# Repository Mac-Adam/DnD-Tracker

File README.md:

# DnD-Tracker
Repository for my resource tracker for D&amp;D
The premise of this project is to make keeping track of health, spell slots, and other resources quick and simple,
while preserving the vibe of an ttrpg.
It consists of 3 modules. One, keeps track of your health (3 led strips each one representing one digit of a 3 digit number)
Second one keeps track of your spell slots
The last one keeps track of whatever 20 resources you have, potions class features, magic items etc.
The rgb leds are driven by a 555 timer based circuit, this allows for controlling the color and brightness of the lights.
A standard 18650 cell is enough to power it for tens of hours (depending on the brightness level)
This project is not yet fully finished, the pcb and the files contain some errors that I haven't fixed yet.
The errors are:
  - Didn't reverse the logic of the LED ON button, insead of turning the leds off, it blasts them at full power
  - Transistors in one of the signal reperaters in the HP modules are switched (P is in flsae of N and N is in place of P)
  - The housing has misaligned mounting holes
## The Future
I might make the design modular, this would enable greater flexibility and probably would be cheaper.
Making the housing more practical and prettier.

If you want to build one of those yoursellf, but you encounter some problems with the provided files, contact me.

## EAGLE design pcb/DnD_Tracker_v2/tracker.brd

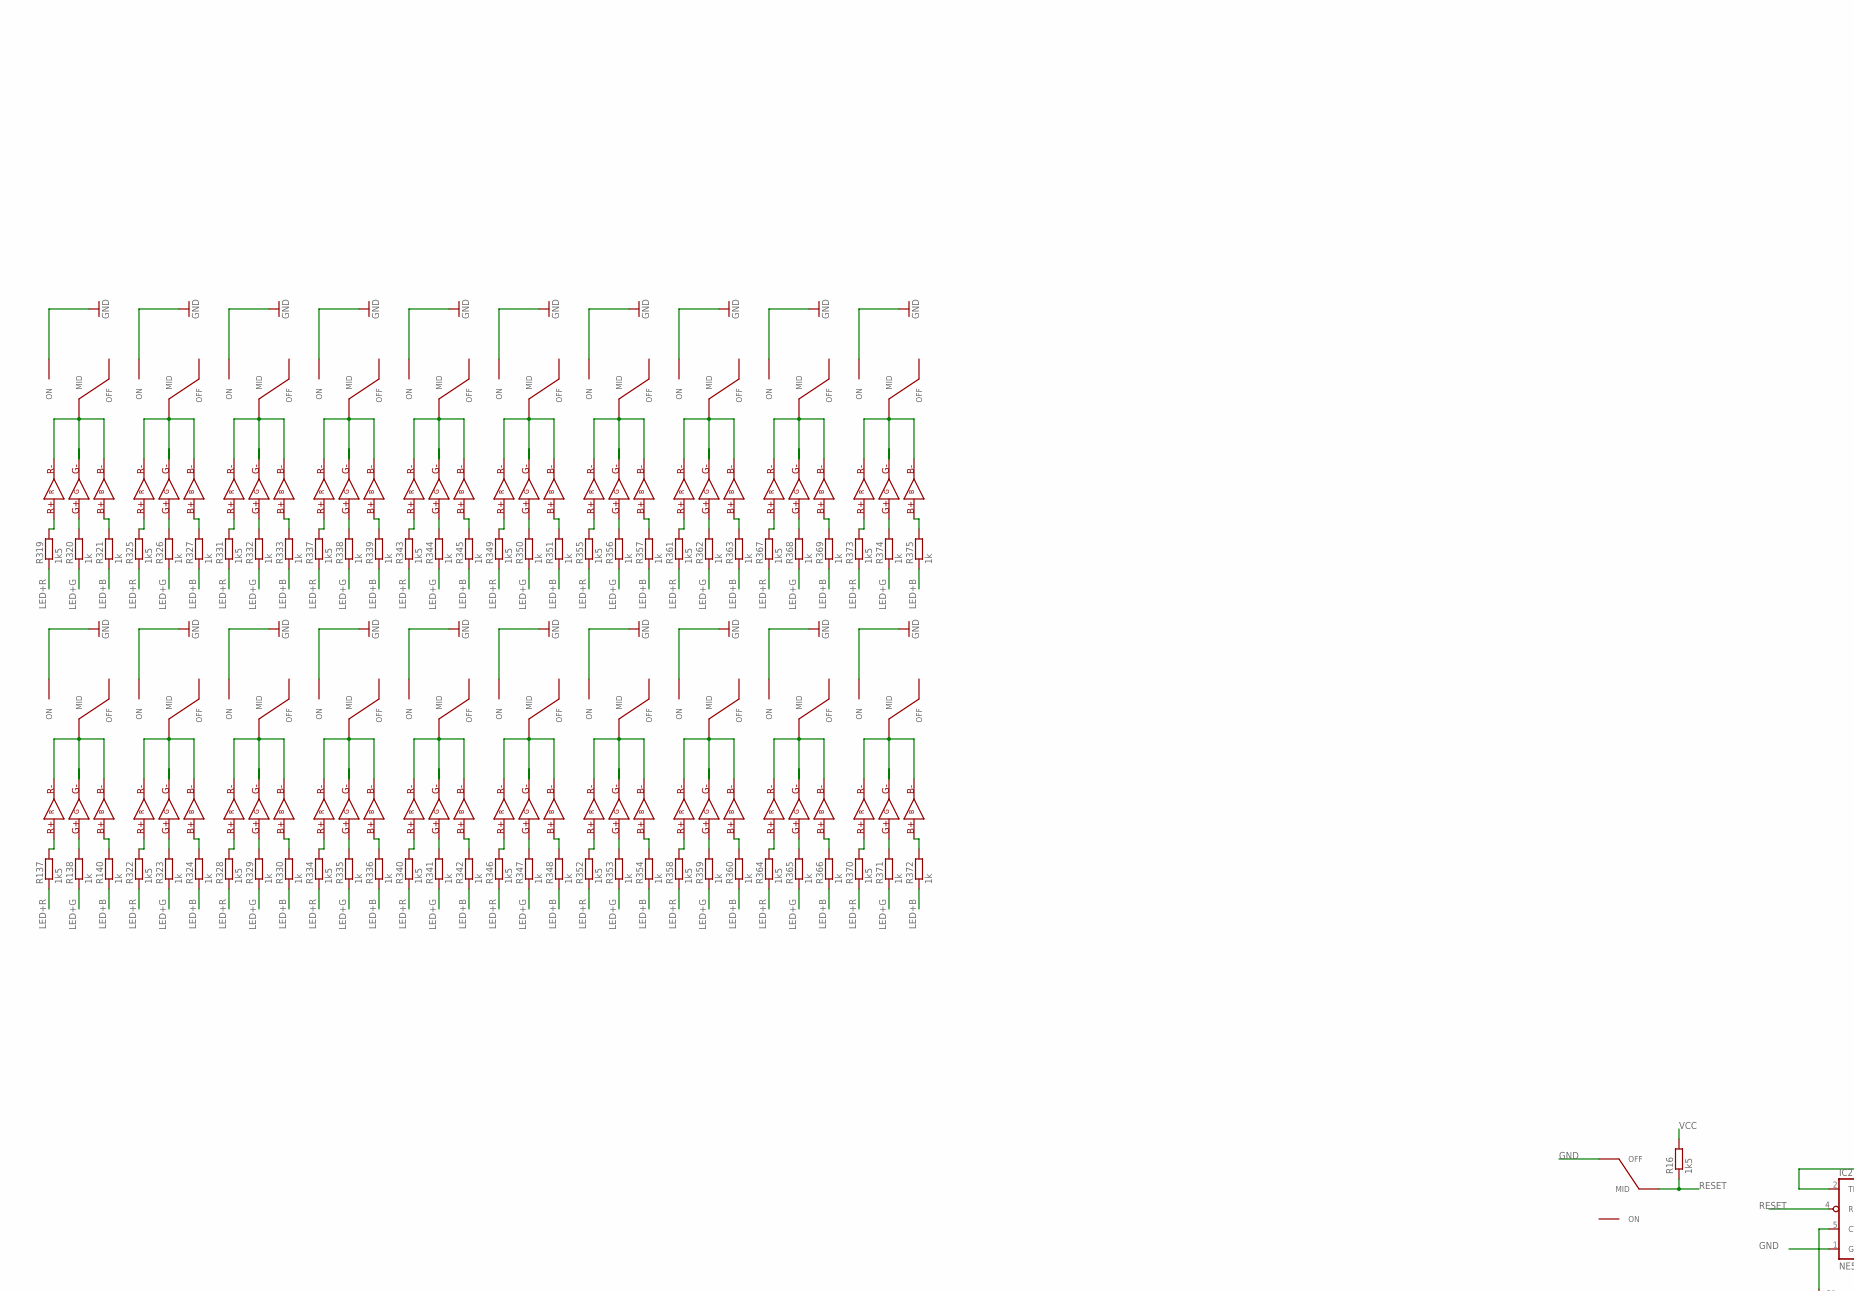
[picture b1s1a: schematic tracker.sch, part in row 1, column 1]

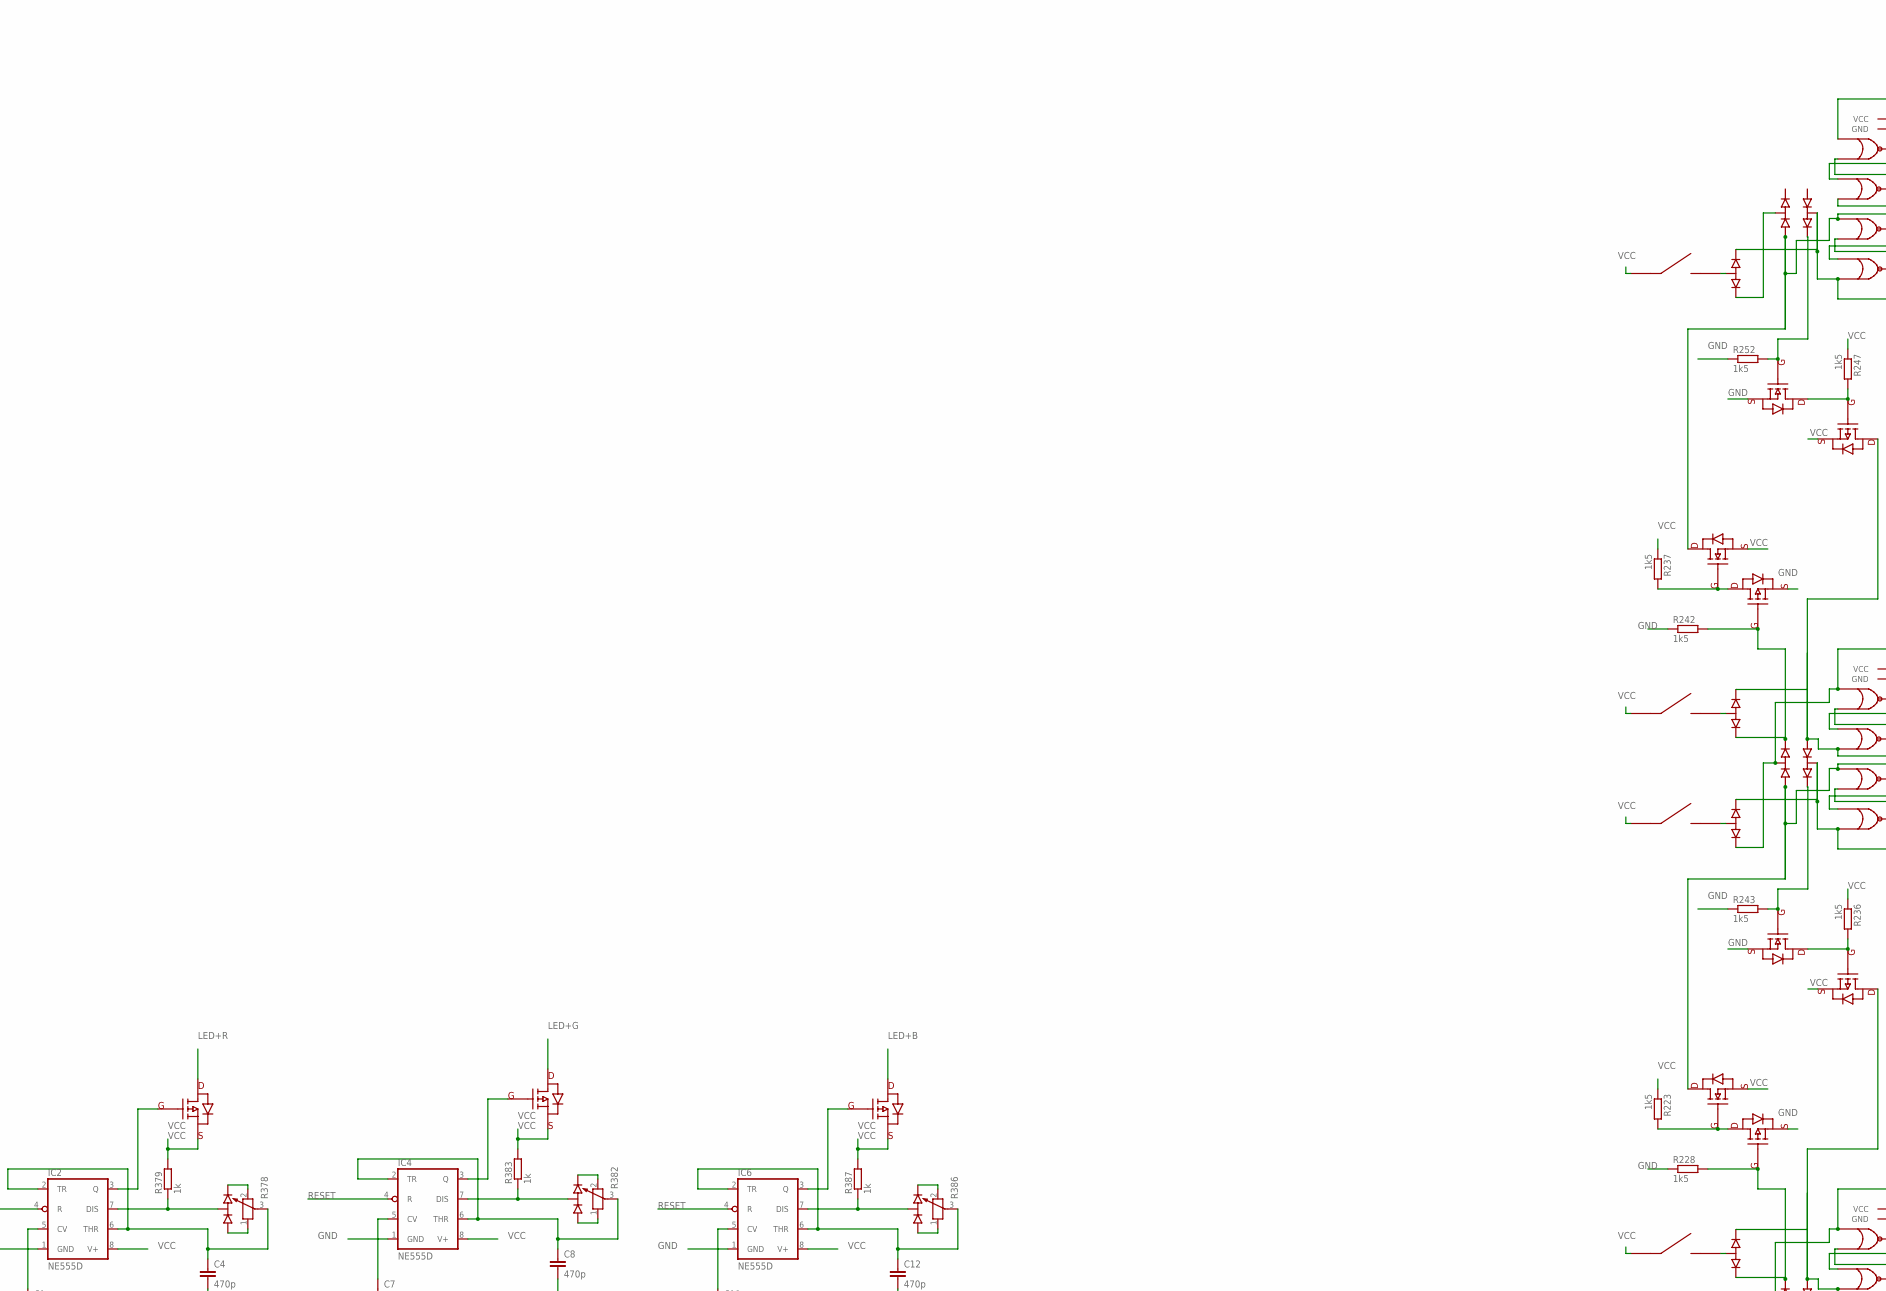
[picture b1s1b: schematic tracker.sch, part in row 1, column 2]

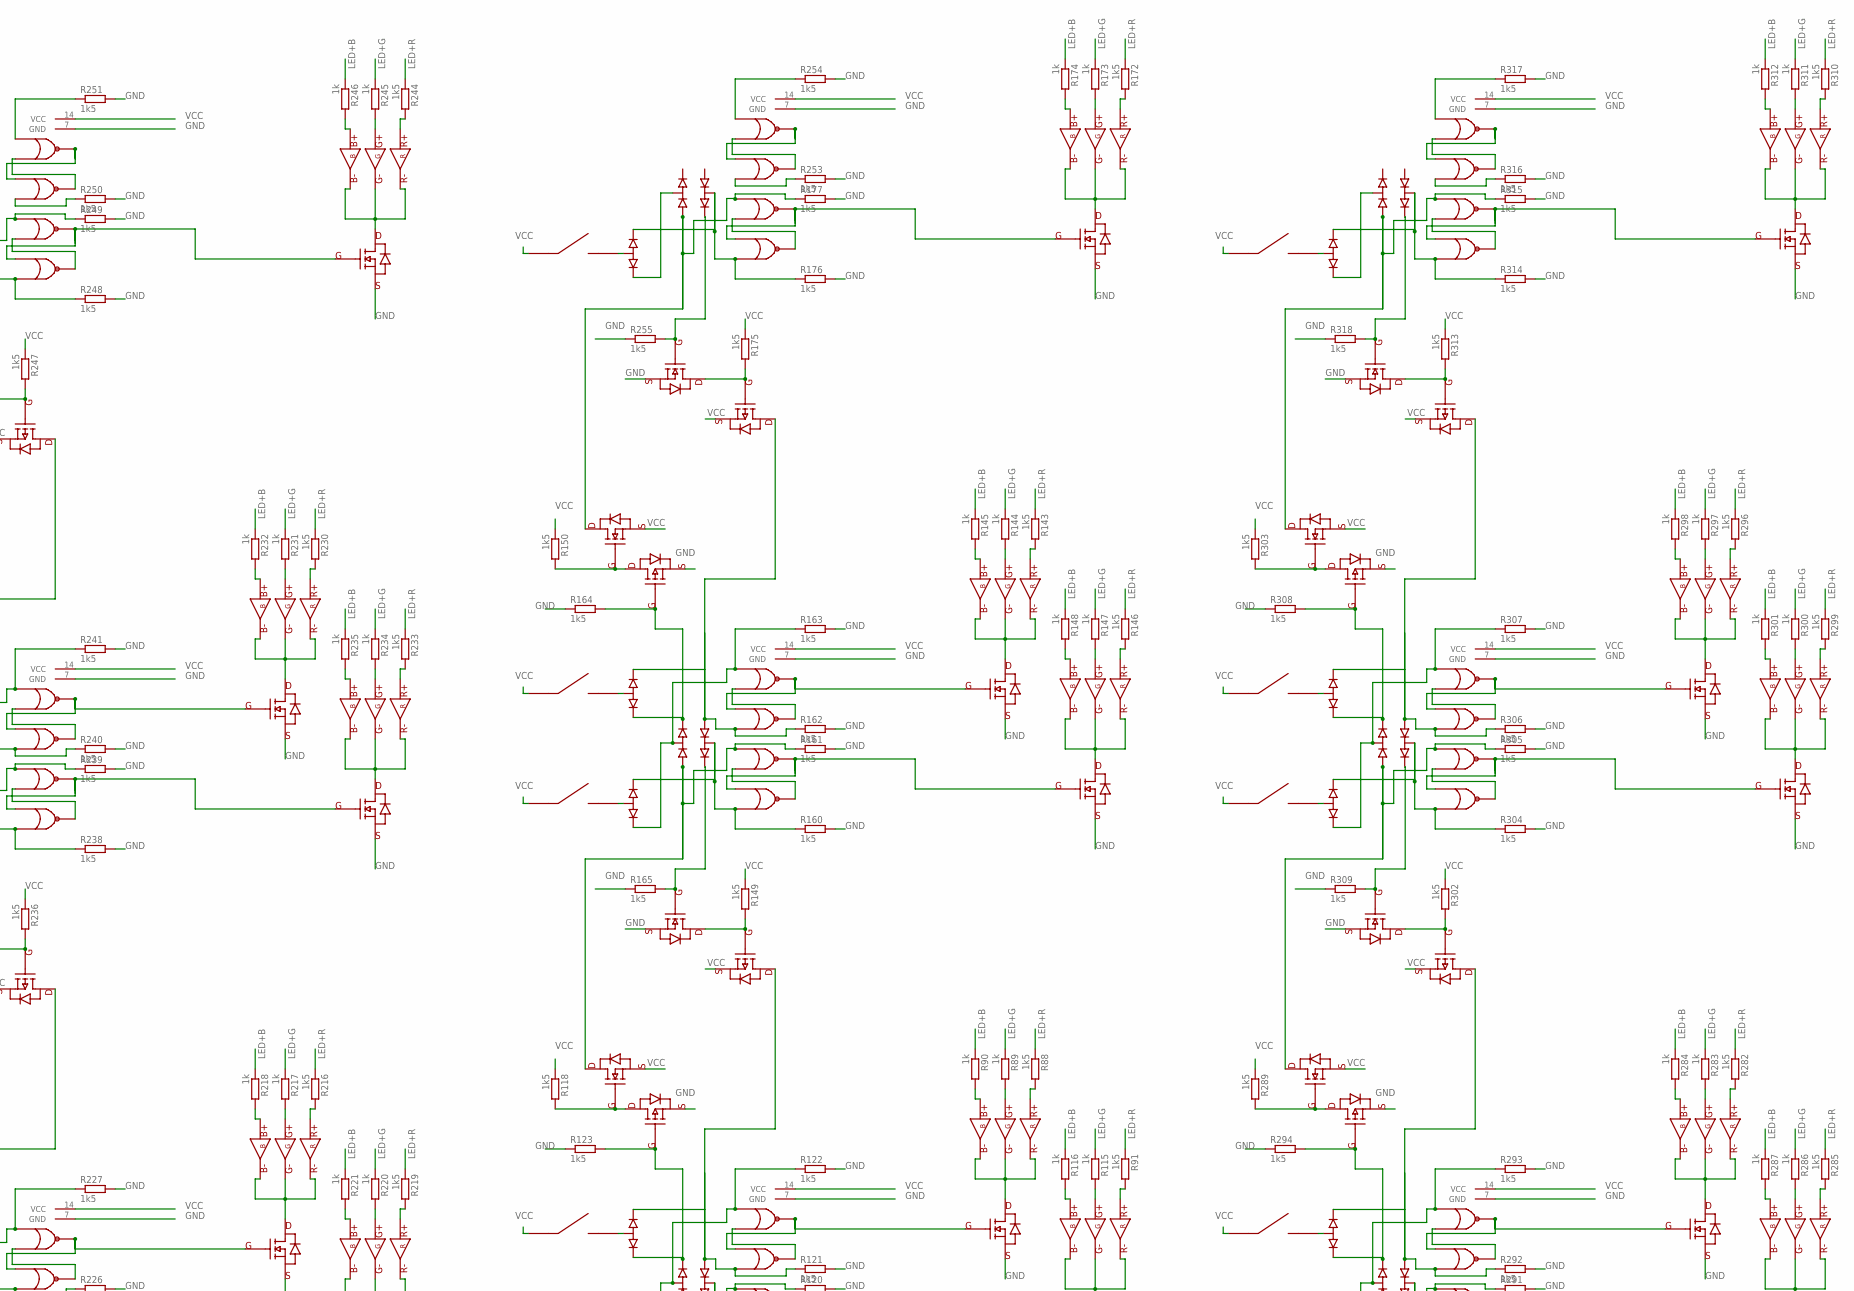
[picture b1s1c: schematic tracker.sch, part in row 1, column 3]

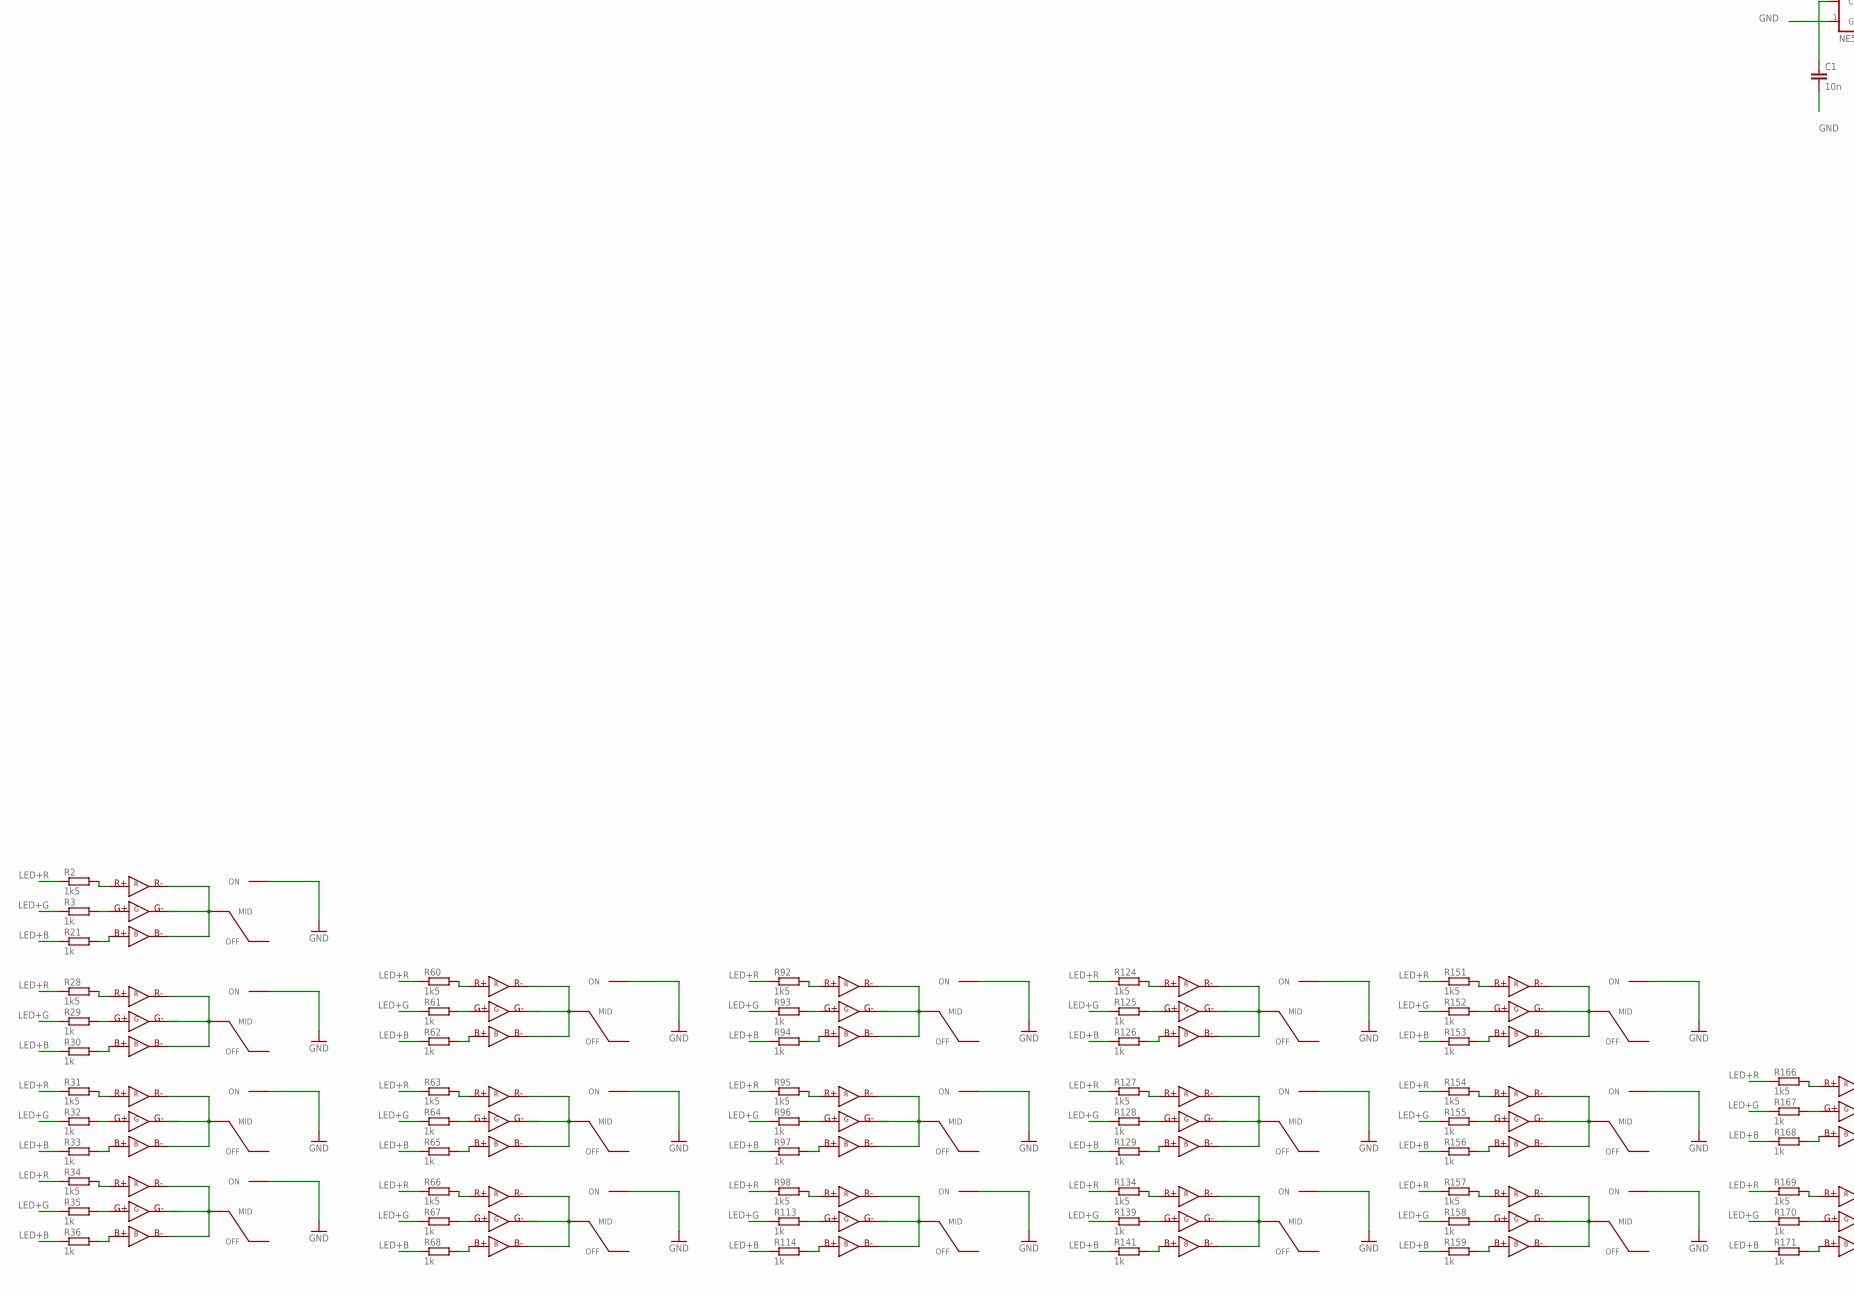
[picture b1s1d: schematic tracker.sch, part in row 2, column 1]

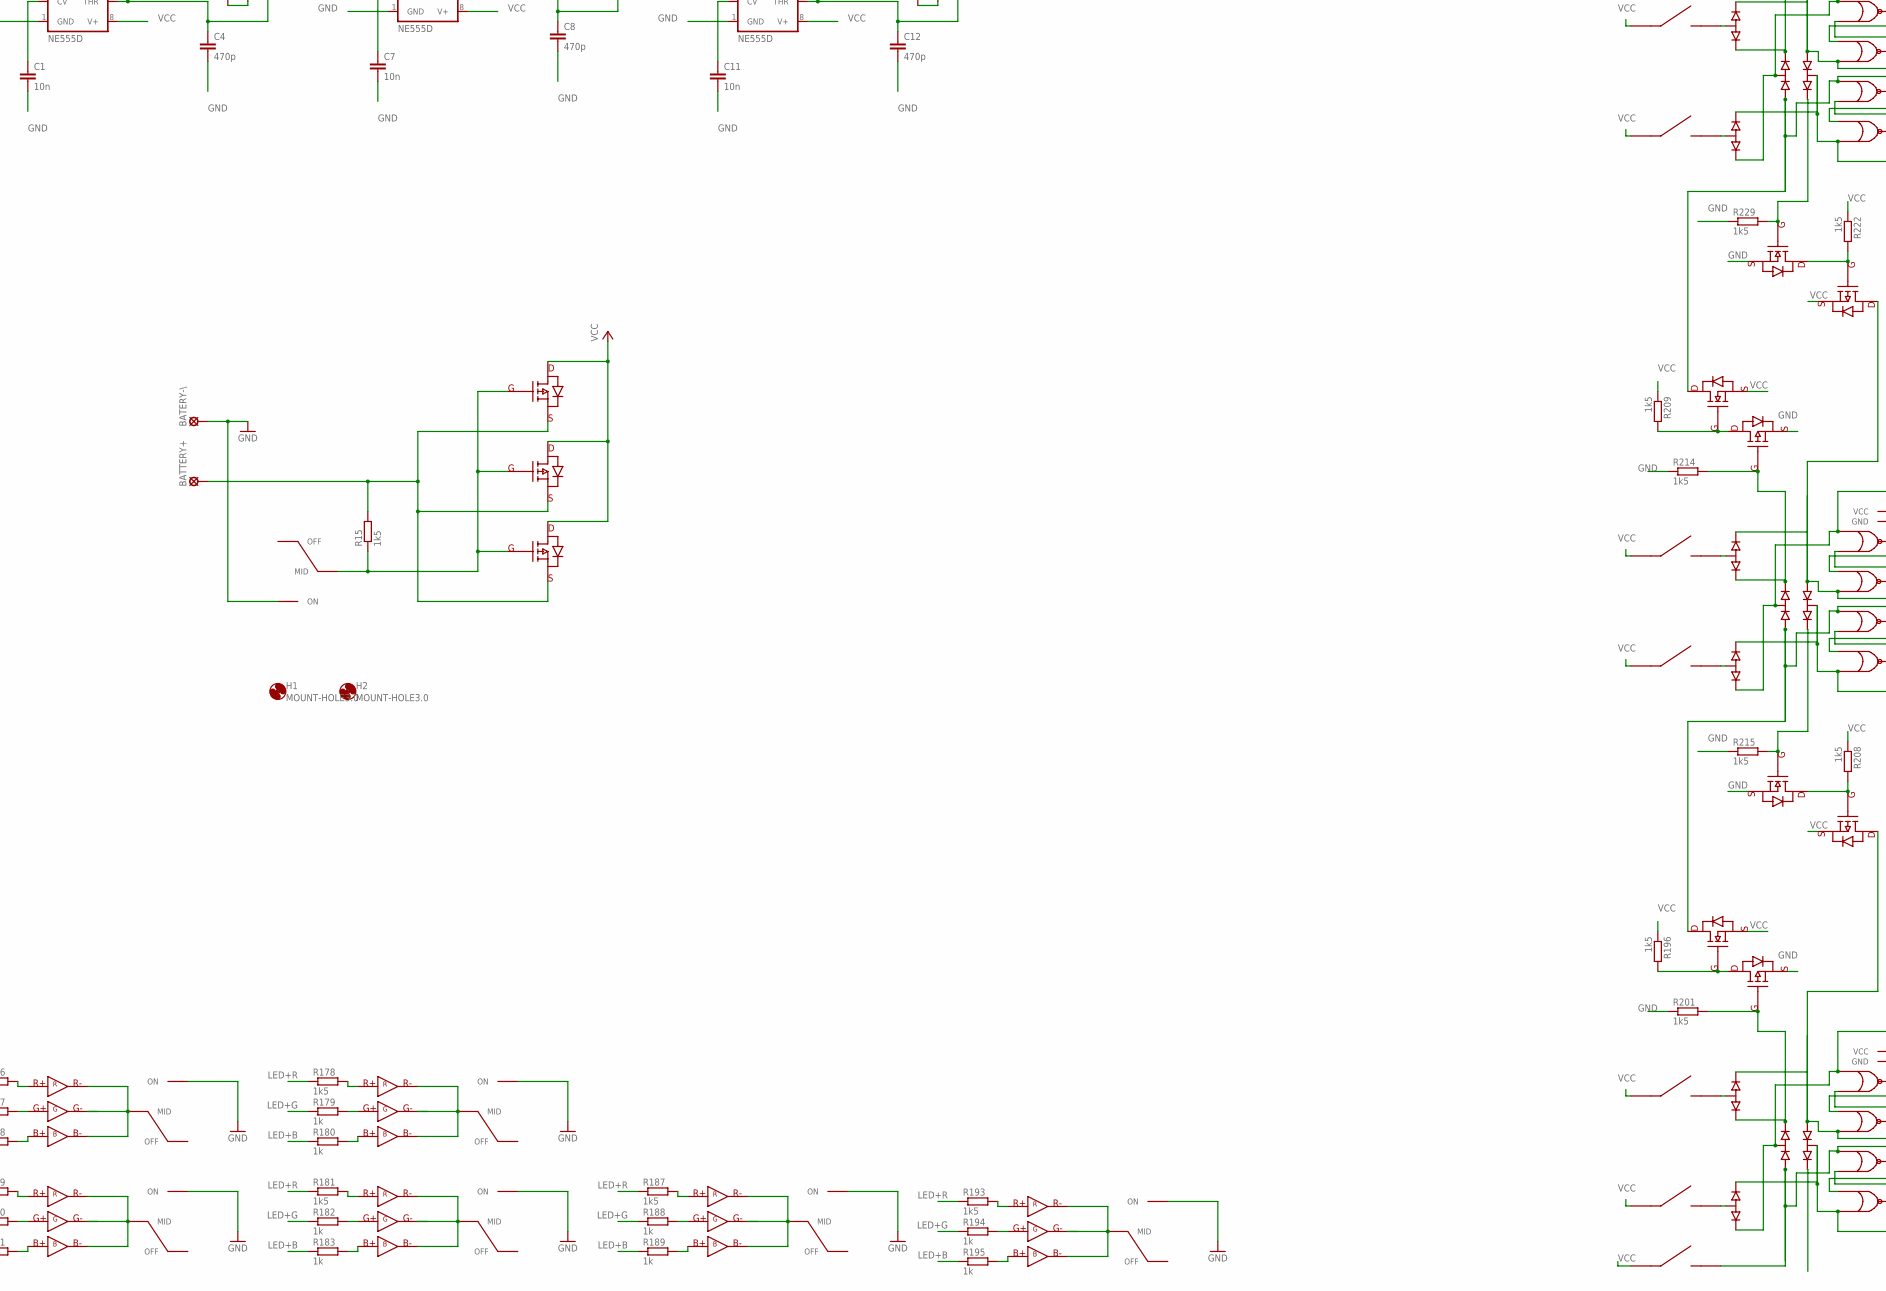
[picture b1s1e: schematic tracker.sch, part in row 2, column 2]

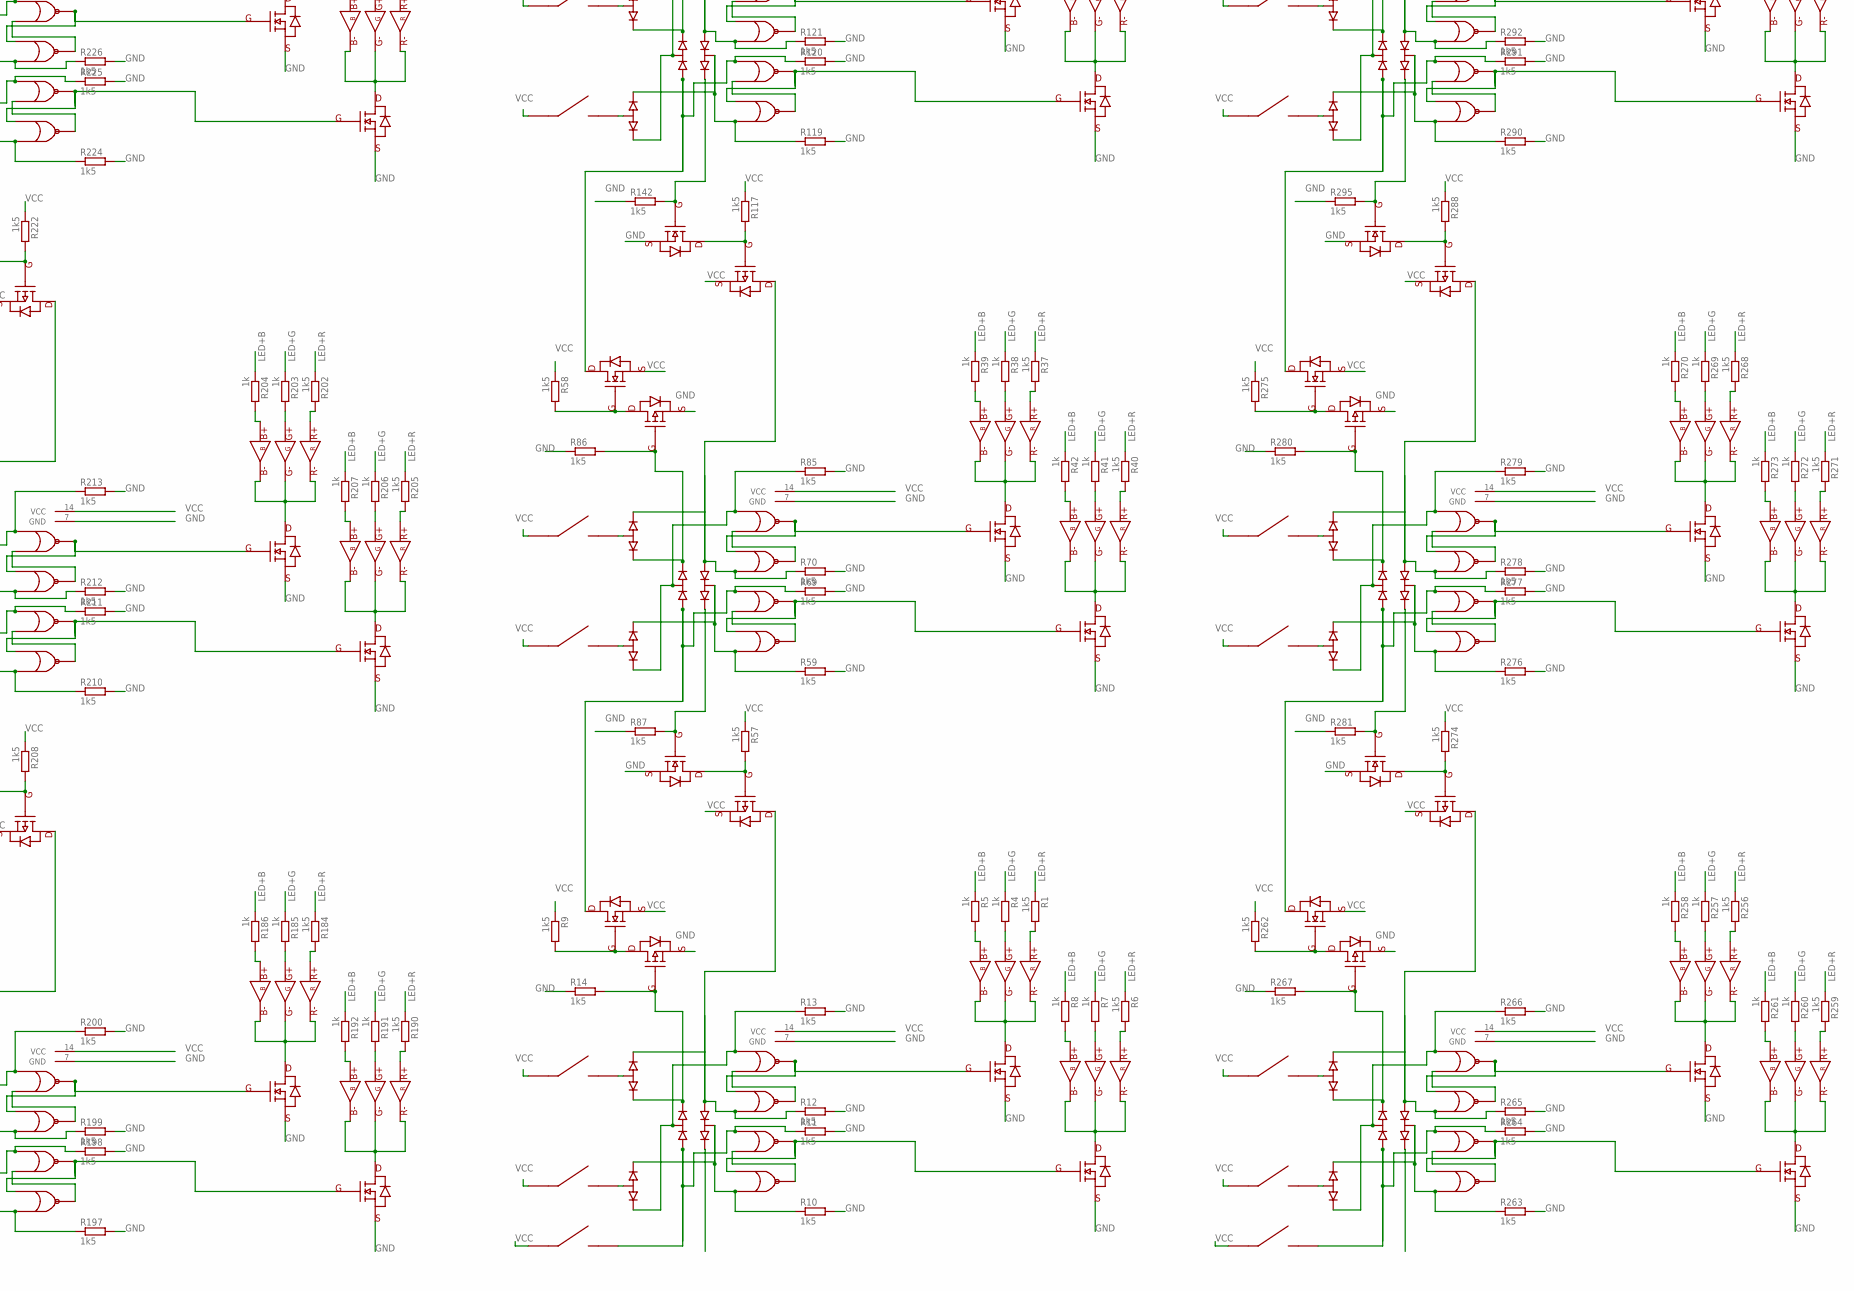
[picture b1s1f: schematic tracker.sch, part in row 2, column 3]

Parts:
BATERY-\: LSP10
BATTERY+: LSP10
C1, C7, C11: 10n; C2012
C4, C8, C12: 470p; C3216
H1, H2: MOUNT-HOLE3.0; 3,0
IC2, IC4, IC6: NE555D; SO08
R1, R2, R6, R9, R10, R11, R12, R13, R14, R15, R16, R28, R31, R34, R37, R40, R57, R58, R59, R60, R63, R66, R69, R70, R85, R86, R87, R88, R91, R92, R95, R98, R117, R118, R119, R120, R121, R122, R123, R124, R127, R134, R137, R142, R143, R146, R149, R150, R151, R154, R157, R160, R161, R162, R163, R164, R165, R166, R169, R172, R175, R176, R177, R178, R181, R184, R187, R190, R193, R196, R197, R198, R199, R200, R201, R202, R205, R208, R209, R210, R211, R212, R213, R214, R215, R216, R219, R222, R223, R224, R225, R226, R227, R228, R229, R230, R233, R236, R237, R238, R239, R240, R241, R242, R243, R244, R247, R248, R249, R250, R251, R252, R253, R254, R255, R256, R259, R262, R263, R264, R265, R266, R267, R268, R271, R274, R275, R276, R277, R278, R279, R280, R281, R282, R285, R288, R289, R290, R291, R292, R293, R294, R295, R296, R299, R302, R303, R304, R305, R306, R307, R308, R309, R310, R313, R314, R315, R316, R317, R318, R319, R322, R325, R328, R331, R334, R337, R340, R343, R346, R349, R352, R355, R358, R361, R364, R367, R370, R373: 1k5; R0402
R3, R4, R5, R7, R8, R21, R29, R30, R32, R33, R35, R36, R38, R39, R41, R42, R61, R62, R64, R65, R67, R68, R89, R90, R93, R94, R96, R97, R113, R114, R115, R116, R125, R126, R128, R129, R138, R139, R140, R141, R144, R145, R147, R148, R152, R153, R155, R156, R158, R159, R167, R168, R170, R171, R173, R174, R179, R180, R182, R183, R185, R186, R188, R189, R191, R192, R194, R195, R203, R204, R206, R207, R217, R218, R220, R221, R231, R232, R234, R235, R245, R246, R257, R258, R260, R261, R269, R270, R272, R273, R283, R284, R286, R287, R297, R298, R300, R301, R311, R312, R320, R321, R323, R324, R326, R327, R329, R330, R332, R333, R335, R336, R338, R339, R341, R342, R344, R345, R347, R348, R350, R351, R353, R354, R356, R357, R359, R360, R362, R363, R365, R366, R368, R369, R371, R372, R374, R375, R379, R383, R387: 1k; R0402
R378, R382, R386: POTENTIOMETER_PT-10; PT-10
U$1, U$2, U$3, U$35, U$97, U$98, U$165, U$179, U$180, U$194, U$195, U$209, U$210, U$219, U$222, U$223, U$237, U$238, U$247, U$261, U$275, U$276, U$290, U$291, U$305, U$306, U$315, U$331, U$335, U$339: YJL2301D_PMOSFET; SOT23
U$4, U$36, U$99, U$148, U$166, U$181, U$196, U$211, U$224, U$239, U$249, U$262, U$277, U$292, U$307: 74HC02PW_QUAD_NOR; TSSOP14
U$5, U$6, U$57, U$59, U$100, U$101, U$150, U$153, U$167, U$168, U$182, U$183, U$197, U$198, U$212, U$213, U$225, U$226, U$240, U$241, U$250, U$251, U$263, U$264, U$278, U$279, U$293, U$294, U$308, U$309, U$332, U$336, U$340: BAT54SW_SERIES_DIODES; SOT323
U$7, U$8, U$60, U$61, U$102, U$124, U$154, U$157, U$169, U$170, U$184, U$185, U$199, U$200, U$214, U$220, U$227, U$228, U$242, U$248, U$252, U$253, U$265, U$266, U$280, U$281, U$295, U$296, U$310, U$316: SMD_MOCROSWITCH; SMD_MICROSWITCH
U$9, U$10, U$62, U$63, U$125, U$126, U$158, U$159, U$171, U$172, U$186, U$187, U$201, U$202, U$215, U$229, U$230, U$243, U$254, U$255, U$267, U$268, U$282, U$283, U$297, U$298, U$311: BAT5406W_COMON_CATHODE_DIODES; SOT323
U$11, U$12, U$22, U$25, U$27, U$29, U$37, U$39, U$43, U$64, U$66, U$68, U$87, U$89, U$91, U$93, U$95, U$103, U$105, U$106, U$108, U$110, U$112, U$114, U$116, U$118, U$120, U$122, U$128, U$130, U$137, U$139, U$140, U$143, U$144, U$147, U$151, U$155, U$317, U$319, U$321, U$323, U$325, U$327: BISTABLESWITCH; BISTABLE_SWITCH
U$20, U$31, U$34, U$70, U$71, U$74, U$75, U$127, U$132, U$135, U$160, U$161, U$164, U$173, U$174, U$177, U$178, U$188, U$189, U$192, U$193, U$203, U$204, U$207, U$208, U$216, U$218, U$221, U$231, U$232, U$235, U$236, U$244, U$246, U$256, U$257, U$260, U$269, U$270, U$273, U$274, U$284, U$285, U$288, U$289, U$299, U$300, U$303, U$304, U$312, U$314: YJL2304A_NMOSFET; SOT23@1
U$24, U$26, U$28, U$30, U$32, U$33, U$38, U$40, U$44, U$65, U$67, U$69, U$72, U$73, U$88, U$90, U$92, U$94, U$96, U$104, U$107, U$109, U$111, U$113, U$115, U$117, U$119, U$121, U$123, U$129, U$131, U$133, U$134, U$136, U$138, U$141, U$142, U$145, U$146, U$149, U$152, U$156, U$162, U$163, U$175, U$176, U$190, U$191, U$205, U$206, U$217, U$233, U$234, U$245, U$258, U$259, U$271, U$272, U$286, U$287, U$301, U$302, U$313, U$318, U$320, U$322, U$324, U$326, U$328: TC5050RGB_LED; BIG_SMD_LED

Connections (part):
CARRY_RESET_IN2: R198.1, U$148.8 (A3), U$150.1WIDEL (IN), U$220.3 (2), U$220.4 (2)
CARRY_RESET_IN3: R11.1, U$4.8 (A3), U$5.1WIDEL (IN), U$248.3 (2), U$248.4 (2)
CARRY_RESET_IN4: R264.1, U$249.8 (A3), U$250.1WIDEL (IN), U$316.3 (2), U$316.4 (2)
CARRY_RESET_OUT2: R211.1, U$164.SINGLE1 (D), U$166.8 (A3), U$167.1WIDEL (IN)
CARRY_RESET_OUT4: R225.1, U$178.SINGLE1 (D), U$181.8 (A3), U$182.1WIDEL (IN)
CARRY_RESET_OUT6: R239.1, U$193.SINGLE1 (D), U$196.8 (A3), U$197.1WIDEL (IN)
CARRY_RESET_OUT8: R249.1, U$208.SINGLE1 (D), U$211.8 (A3), U$212.1WIDEL (IN)
CARRY_RESET_OUT9: R69.1, U$34.SINGLE1 (D), U$36.8 (A3), U$57.1WIDEL (IN)
CARRY_RESET_OUT10: R120.1, U$75.SINGLE1 (D), U$99.8 (A3), U$100.1WIDEL (IN)
CARRY_RESET_OUT11: R161.1, U$221.SINGLE1 (D), U$224.8 (A3), U$225.1WIDEL (IN)
CARRY_RESET_OUT12: R177.1, U$236.SINGLE1 (D), U$239.8 (A3), U$240.1WIDEL (IN)
CARRY_RESET_OUT13: R277.1, U$260.SINGLE1 (D), U$262.8 (A3), U$263.1WIDEL (IN)
CARRY_RESET_OUT14: R291.1, U$274.SINGLE1 (D), U$277.8 (A3), U$278.1WIDEL (IN)
CARRY_RESET_OUT15: R305.1, U$289.SINGLE1 (D), U$292.8 (A3), U$293.1WIDEL (IN)
CARRY_RESET_OUT16: R315.1, U$304.SINGLE1 (D), U$307.8 (A3), U$308.1WIDEL (IN)
CARRY_SET_IN1: R250.1, U$211.6 (B2)
CARRY_SET_IN2: R253.1, U$239.6 (B2)
CARRY_SET_IN3: R316.1, U$307.6 (B2)
CARRY_SET_OUT1: R199.1, U$148.6 (B2), U$153.1WIDEL (IN), U$158.2WIDER (OUT1), U$179.SINGLE1 (D)
CARRY_SET_OUT2: R212.1, U$166.6 (B2), U$168.1WIDEL (IN), U$171.2WIDER (OUT1), U$194.SINGLE1 (D)
CARRY_SET_OUT4: R226.1, U$181.6 (B2), U$183.1WIDEL (IN), U$186.2WIDER (OUT1), U$209.SINGLE1 (D)
CARRY_SET_OUT6: R240.1, U$196.6 (B2), U$198.1WIDEL (IN), U$201.2WIDER (OUT1), U$219.SINGLE1 (D)
CARRY_SET_OUT8: R12.1, U$4.6 (B2), U$6.1WIDEL (IN), U$9.2WIDER (OUT1), U$97.SINGLE1 (D)
CARRY_SET_OUT10: R70.1, U$36.6 (B2), U$59.1WIDEL (IN), U$62.2WIDER (OUT1), U$222.SINGLE1 (D)
CARRY_SET_OUT11: R121.1, U$99.6 (B2), U$101.1WIDEL (IN), U$125.2WIDER (OUT1), U$237.SINGLE1 (D)
CARRY_SET_OUT12: R162.1, U$224.6 (B2), U$226.1WIDEL (IN), U$229.2WIDER (OUT1), U$247.SINGLE1 (D)
CARRY_SET_OUT13: R265.1, U$249.6 (B2), U$251.1WIDEL (IN), U$254.2WIDER (OUT1), U$275.SINGLE1 (D)
CARRY_SET_OUT14: R278.1, U$262.6 (B2), U$264.1WIDEL (IN), U$267.2WIDER (OUT1), U$290.SINGLE1 (D)
CARRY_SET_OUT15: R292.1, U$277.6 (B2), U$279.1WIDEL (IN), U$282.2WIDER (OUT1), U$305.SINGLE1 (D)
CARRY_SET_OUT16: R306.1, U$292.6 (B2), U$294.1WIDEL (IN), U$297.2WIDER (OUT1), U$315.SINGLE1 (D)
ENB2: U$148.1 (Y1), U$148.5 (A2), U$160.WIDEL (G)
ENB4: U$166.1 (Y1), U$166.5 (A2), U$173.WIDEL (G)
ENB6: U$181.1 (Y1), U$181.5 (A2), U$188.WIDEL (G)
ENB8: U$196.1 (Y1), U$196.5 (A2), U$203.WIDEL (G)
ENB10: U$211.1 (Y1), U$211.5 (A2)
ENB11: U$4.1 (Y1), U$4.5 (A2), U$20.WIDEL (G)
ENB12: U$36.1 (Y1), U$36.5 (A2), U$70.WIDEL (G)
ENB13: U$99.1 (Y1), U$99.5 (A2), U$127.WIDEL (G)
ENB14: U$224.1 (Y1), U$224.5 (A2), U$231.WIDEL (G)
ENB15: U$239.1 (Y1), U$239.5 (A2)
ENB16: U$249.1 (Y1), U$249.5 (A2), U$256.WIDEL (G)
ENB17: U$262.1 (Y1), U$262.5 (A2), U$269.WIDEL (G)
ENB18: U$277.1 (Y1), U$277.5 (A2), U$284.WIDEL (G)
ENB19: U$292.1 (Y1), U$292.5 (A2), U$299.WIDEL (G)
ENB20: U$307.1 (Y1), U$307.5 (A2)
GND: BATERY-\.MP, C1.2, C4.2, C7.2, C8.2, C11.2, C12.2, IC2.1 (GND), IC4.1 (GND), IC6.1 (GND), R10.2, R11.2, R12.2, R13.2, R14.1, R59.2, R69.2, R70.2, R85.2, R86.1, R87.1, R119.2, R120.2, R121.2, R122.2, R123.1, R142.1, R160.2, R161.2, R162.2, R163.2, R164.1, R165.1, R176.2, R177.2, R197.2, R198.2, R199.2, R200.2, R201.1, R210.2, R211.2, R212.2, R213.2, R214.1, R215.1, R224.2, R225.2, R226.2, R227.2, R228.1, R229.1, R238.2, R239.2, R240.2, R241.2, R242.1, R243.1, R248.2, R249.2, R250.2, R251.2, R252.1, R253.2, R254.2, R255.1, R263.2, R264.2, R265.2, R266.2, R267.1, R276.2, R277.2, R278.2, R279.2, R280.1, R281.1, R290.2, R291.2, R292.2, R293.2, R294.1, R295.1, R304.2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
LED+B: R5.1, R8.1, R21.1, R30.1, R33.1, R36.1, R39.1, R42.1, R62.1, R65.1, R68.1, R90.1, R94.1, R97.1, R114.1, R116.1, R126.1, R129.1, R140.1, R141.1, R145.1, R148.1, R153.1, R156.1, R159.1, R168.1, R171.1, R174.1, R180.1, R183.1, R186.1, R189.1, R192.1, R195.1, R204.1, R207.1, R218.1, R221.1, R232.1, R235.1, R246.1, R258.1, R261.1, R270.1, R273.1, R284.1, R287.1, R298.1, R301.1, R312.1, R321.1, R324.1, R327.1, R330.1, R333.1, R336.1, R339.1, R342.1, R345.1, R348.1, R351.1, R354.1, R357.1, R360.1, R363.1, R366.1, R369.1, R372.1, R375.1, U$339.SINGLE1 (D)
LED+G: R3.1, R4.1, R7.1, R29.1, R32.1, R35.1, R38.1, R41.1, R61.1, R64.1, R67.1, R89.1, R93.1, R96.1, R113.1, R115.1, R125.1, R128.1, R138.1, R139.1, R144.1, R147.1, R152.1, R155.1, R158.1, R167.1, R170.1, R173.1, R179.1, R182.1, R185.1, R188.1, R191.1, R194.1, R203.1, R206.1, R217.1, R220.1, R231.1, R234.1, R245.1, R257.1, R260.1, R269.1, R272.1, R283.1, R286.1, R297.1, R300.1, R311.1, R320.1, R323.1, R326.1, R329.1, R332.1, R335.1, R338.1, R341.1, R344.1, R347.1, R350.1, R353.1, R356.1, R359.1, R362.1, R365.1, R368.1, R371.1, R374.1, U$335.SINGLE1 (D)
LED+R: R1.1, R2.1, R6.1, R28.1, R31.1, R34.1, R37.1, R40.1, R60.1, R63.1, R66.1, R88.1, R91.1, R92.1, R95.1, R98.1, R124.1, R127.1, R134.1, R137.1, R143.1, R146.1, R151.1, R154.1, R157.1, R166.1, R169.1, R172.1, R178.1, R181.1, R184.1, R187.1, R190.1, R193.1, R202.1, R205.1, R216.1, R219.1, R230.1, R233.1, R244.1, R256.1, R259.1, R268.1, R271.1, R282.1, R285.1, R296.1, R299.1, R310.1, R319.1, R322.1, R325.1, R328.1, R331.1, R334.1, R337.1, R340.1, R343.1, R346.1, R349.1, R352.1, R355.1, R358.1, R361.1, R364.1, R367.1, R370.1, R373.1, U$331.SINGLE1 (D)
N2: R201.2, U$150.2WIDER (OUT), U$158.1WIDEL (OUT2), U$165.WIDEL (G)
N4: R214.2, U$167.2WIDER (OUT), U$171.1WIDEL (OUT2), U$180.WIDEL (G)
N6: R228.2, U$182.2WIDER (OUT), U$186.1WIDEL (OUT2), U$195.WIDEL (G)
N8: R242.2, U$197.2WIDER (OUT), U$201.1WIDEL (OUT2), U$210.WIDEL (G)
N9: R14.2, U$5.2WIDER (OUT), U$9.1WIDEL (OUT2), U$35.WIDEL (G)
N10: R86.2, U$57.2WIDER (OUT), U$62.1WIDEL (OUT2), U$98.WIDEL (G)
N11: R123.2, U$100.2WIDER (OUT), U$125.1WIDEL (OUT2), U$223.WIDEL (G)
N12: R164.2, U$225.2WIDER (OUT), U$229.1WIDEL (OUT2), U$238.WIDEL (G)
N13: R267.2, U$250.2WIDER (OUT), U$254.1WIDEL (OUT2), U$261.WIDEL (G)
N14: R280.2, U$263.2WIDER (OUT), U$267.1WIDEL (OUT2), U$276.WIDEL (G)
N15: R294.2, U$278.2WIDER (OUT), U$282.1WIDEL (OUT2), U$291.WIDEL (G)
N16: R308.2, U$293.2WIDER (OUT), U$297.1WIDEL (OUT2), U$306.WIDEL (G)
unnamed: BATTERY+.MP, R15.2, U$1.WIDER (S), U$2.WIDER (S), U$3.WIDER (S)
unnamed: U$4.3 (B1), U$4.4 (Y2)
unnamed: U$4.9 (B3), U$4.13 (Y4)
unnamed: U$4.10 (Y3), U$4.11 (A4), U$31.WIDEL (G)
unnamed: R10.1, U$4.12 (B4), U$6.3SINGLE (MID), U$10.2WIDER (OUT1)
unnamed: U$7.3 (2), U$7.4 (2), U$9.3SINGLE (IN1)
unnamed: R15.1, U$1.WIDEL (G), U$2.WIDEL (G), U$3.WIDEL (G), U$11.A2 (MID), U$11.B2 (MID)
unnamed: U$8.3 (2), U$8.4 (2), U$10.3SINGLE (IN1)
unnamed: R13.1, U$4.2 (A1), U$5.3SINGLE (MID), U$10.1WIDEL (OUT2)
unnamed: R1.2, U$32.2 (RPLUS)
unnamed: R4.2, U$32.1 (GPLUS)
unnamed: R5.2, U$32.3 (BPLUS)
unnamed: U$20.SINGLE1 (D), U$32.4 (BMINUS), U$32.5 (RMINUS), U$32.6 (GMINUS)
unnamed: R6.2, U$33.2 (RPLUS)
unnamed: R7.2, U$33.1 (GPLUS)
unnamed: R8.2, U$33.3 (BPLUS)
unnamed: U$31.SINGLE1 (D), U$33.4 (BMINUS), U$33.5 (RMINUS), U$33.6 (GMINUS)
unnamed: R2.2, U$24.2 (RPLUS)
unnamed: R3.2, U$24.1 (GPLUS)
unnamed: R21.2, U$24.3 (BPLUS)
unnamed: U$22.A2 (MID), U$22.B2 (MID), U$24.4 (BMINUS), U$24.5 (RMINUS), U$24.6 (GMINUS)
unnamed: R28.2, U$26.2 (RPLUS)
unnamed: R29.2, U$26.1 (GPLUS)
unnamed: R30.2, U$26.3 (BPLUS)
unnamed: U$25.A2 (MID), U$25.B2 (MID), U$26.4 (BMINUS), U$26.5 (RMINUS), U$26.6 (GMINUS)
unnamed: R31.2, U$28.2 (RPLUS)
unnamed: R32.2, U$28.1 (GPLUS)
unnamed: R33.2, U$28.3 (BPLUS)
unnamed: U$27.A2 (MID), U$27.B2 (MID), U$28.4 (BMINUS), U$28.5 (RMINUS), U$28.6 (GMINUS)
unnamed: R34.2, U$30.2 (RPLUS)
unnamed: R35.2, U$30.1 (GPLUS)
unnamed: R36.2, U$30.3 (BPLUS)
unnamed: U$29.A2 (MID), U$29.B2 (MID), U$30.4 (BMINUS), U$30.5 (RMINUS), U$30.6 (GMINUS)
unnamed: R9.2, U$34.WIDEL (G), U$35.SINGLE1 (D)
unnamed: U$36.3 (B1), U$36.4 (Y2)
unnamed: U$36.9 (B3), U$36.13 (Y4)
unnamed: U$36.10 (Y3), U$36.11 (A4), U$71.WIDEL (G)
unnamed: R59.1, U$36.12 (B4), U$59.3SINGLE (MID), U$63.2WIDER (OUT1)
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
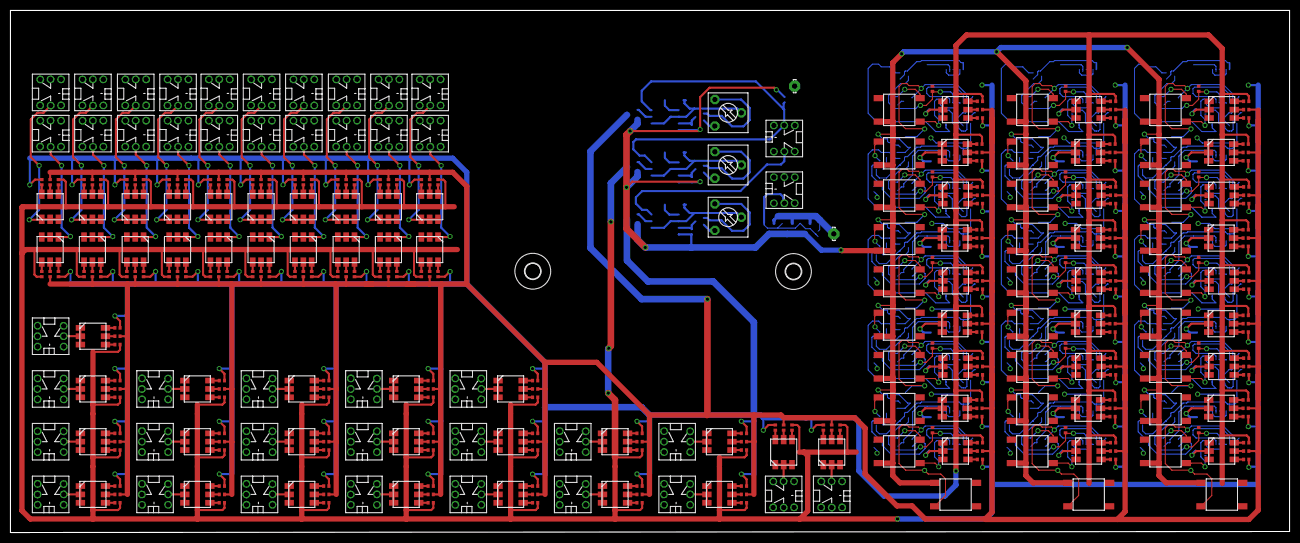
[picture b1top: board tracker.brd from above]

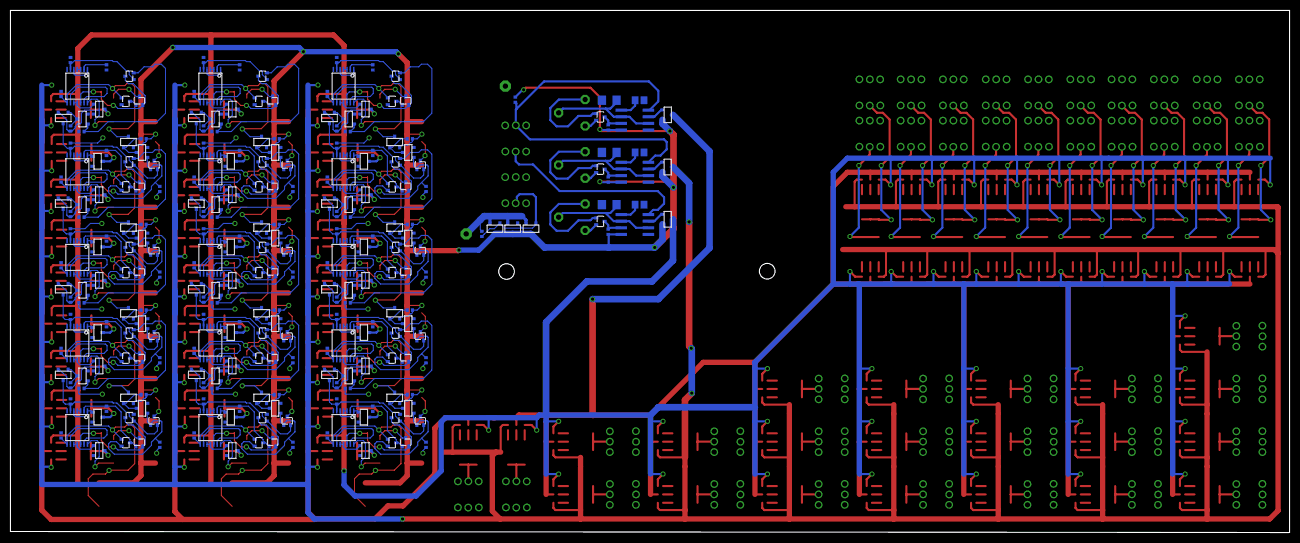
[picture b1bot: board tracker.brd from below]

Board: 2 copper layers, 245.0 x 100.0 mm, 635 parts (263 on the bottom side), 500 nets.

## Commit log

2024-10-14 file_upload
2024-10-14 added_lib
